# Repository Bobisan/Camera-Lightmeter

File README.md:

# Camera Light Meter
Светломер за фотоапарати, който измерва количеството светлина на околната среда, определя правилната експозиция за снимките и пресмята стойностите на настройките, нужни за нея. Вмомента функцоионално работи, но е на breadboard, има неудобни контроли, работи само сързан към захранване и има неоптимизиран код, който води до проблеми. Целта ни е да намалим цялостният размер на проекта и да увеличим неговата надеждност, като го направим на печатна платка и му 3D принтираме корпус, да подобрим и сменим някои от използваните компоненти, като екрана, който смятаме да сменим с някой по-малък и с по-висока резолюция, и бутоните, които смятаме да сменим с ротационни енкодери за по-компактен и удобен дизайн, и смятаме да го направим да работи на презареждаема батерия.

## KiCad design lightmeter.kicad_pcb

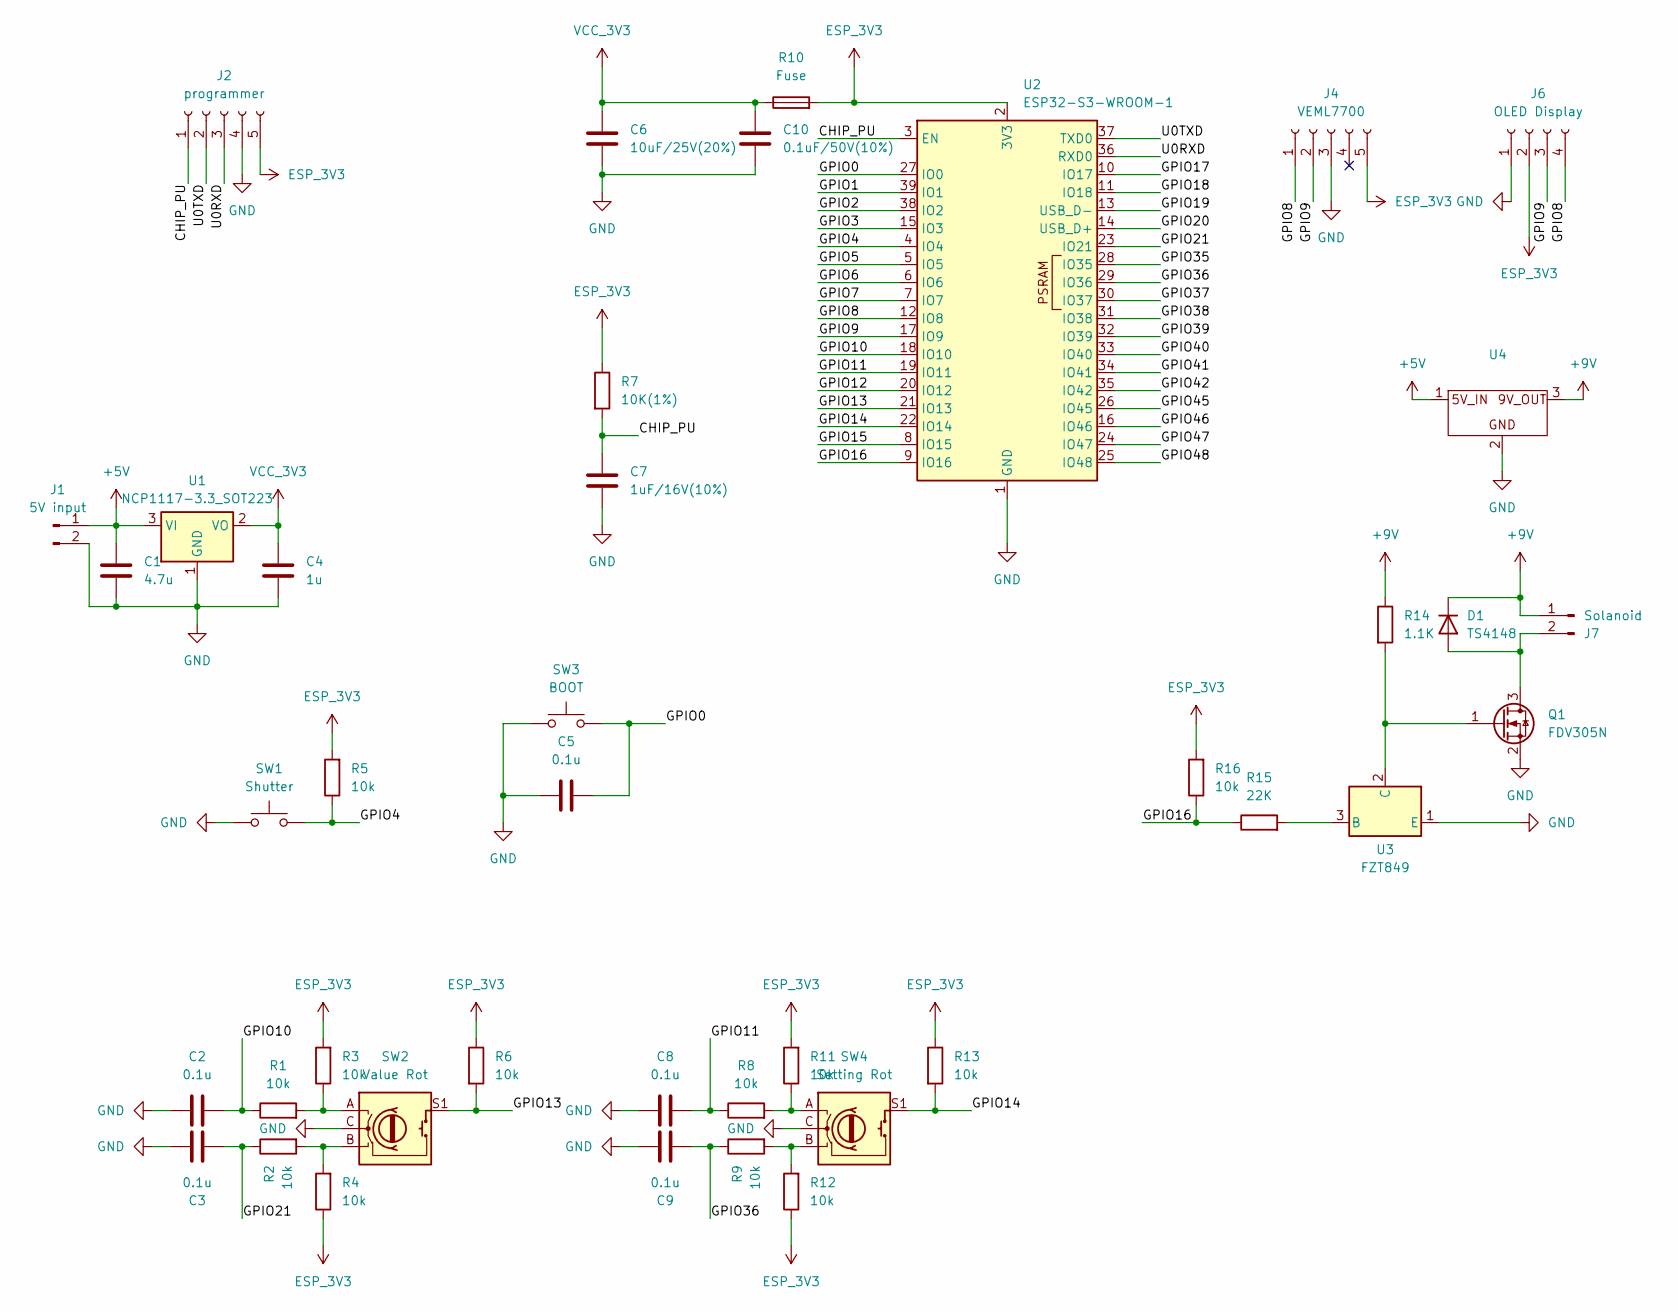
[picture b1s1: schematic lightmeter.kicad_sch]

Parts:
C1: 4.7u; C_0805_2012Metric
C2, C3, C5, C8, C9: 0.1u; C_0805_2012Metric
C4: 1u; C_0805_2012Metric
C6: 10uF/25V(20%); C_0805_2012Metric
C7: 1uF/16V(10%); C_0805_2012Metric
C10: 0.1uF/50V(10%); C_0805_2012Metric
D1: TS4148; D_0805_2012Metric
J1: 5V input; JST_EH_B2B-EH-A_1x02_P2.50mm_Vertical
J2: programmer; JST_EH_B5B-EH-A_1x05_P2.50mm_Vertical
J4: VEML7700; PinHeader_1x05_P2.54mm_Vertical
J6: OLED Display; JST_EH_B4B-EH-A_1x04_P2.50mm_Vertical
J7: Solanoid; JST_EH_B2B-EH-A_1x02_P2.50mm_Vertical
Q1: FDV305N; SOT-23
R1, R2, R3, R4, R5, R6, R8, R9, R11, R12, R13, R16: 10k; R_0805_2012Metric
R7: 10K(1%); R_0805_2012Metric
R10: Fuse; Fuse_1206_3216Metric
R14: 1.1K; R_0805_2012Metric
R15: 22K; R_0805_2012Metric
SW1: Shutter; Vertical_Push_Button
SW2: Value Rot; Rotary_JST
SW3: BOOT; SW_PUSH_1P1T_6x3.5mm_H4.3_APEM_MJTP1243
SW4: Setting Rot; Rotary_JST
U1: NCP1117-3.3_SOT223; SOT-223-3_TabPin2
U2: ESP32-S3-WROOM-1
U3: FZT849; SOT-223-3_TabPin2
U4: Boost_Converter_Module

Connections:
+5V: C1.1, J1.1, U1.3 (VI), U4.1
+9V: D1.1 (K), J7.1, R14.1, U4.3
/CHIP_PU: C7.1, J2.1, R7.2, U2.3 (EN)
/GPIO0: C5.2, SW3.2, U2.27 (IO0)
/GPIO1: U2.39 (IO1)
/GPIO2: U2.38 (IO2)
/GPIO3: U2.15 (IO3)
/GPIO4: R5.1, SW1.2, U2.4 (IO4)
/GPIO5: U2.5 (IO5)
/GPIO6: U2.6 (IO6)
/GPIO7: U2.7 (IO7)
/GPIO8: J4.1, J6.4, U2.12 (IO8)
/GPIO9: J4.2, J6.3, U2.17 (IO9)
/GPIO10: C2.2, R1.1, U2.18 (IO10)
/GPIO11: C8.2, R8.1, U2.19 (IO11)
/GPIO12: U2.20 (IO12)
/GPIO13: R6.2, SW2.S1, U2.21 (IO13)
/GPIO14: R13.2, SW4.S1, U2.22 (IO14)
/GPIO15: U2.8 (IO15)
/GPIO16: R15.1, R16.1, U2.9 (IO16)
/GPIO17: U2.10 (IO17)
/GPIO18: U2.11 (IO18)
/GPIO19: U2.13 (USB_D-)
/GPIO20: U2.14 (USB_D+)
/GPIO21: C3.2, R2.1, U2.23 (IO21)
/GPIO35: U2.28 (IO35)
/GPIO36: C9.2, R9.1, U2.29 (IO36)
/GPIO37: U2.30 (IO37)
/GPIO38: U2.31 (IO38)
/GPIO39: U2.32 (IO39)
/GPIO40: U2.33 (IO40)
/GPIO41: U2.34 (IO41)
/GPIO42: U2.35 (IO42)
/GPIO45: U2.26 (IO45)
/GPIO46: U2.16 (IO46)
/GPIO47: U2.24 (IO47)
/GPIO48: U2.25 (IO48)
/U0RXD: J2.3, U2.36 (RXD0)
/U0TXD: J2.2, U2.37 (TXD0)
ESP_3V3: J2.5, J4.5, J6.2, R3.2, R4.1, R5.2, R6.1, R7.1, R10.2, R11.2, R12.1, R13.1, R16.2, U2.2 (3V3)
GND: C1.2, C2.1, C3.1, C4.2, C5.1, C6.2, C7.2, C8.1, C9.1, C10.2, J1.2, J2.4, J4.3, J6.1, Q1.2 (S), SW1.1, SW2.C, SW3.1, SW4.C, U1.1 (GND), U2.1 (GND), U2.40 (GND), U2.41 (GND), U3.1 (E), U4.2
unnamed: D1.2 (A), J7.2, Q1.3 (D)
unnamed: Q1.1 (G), R14.2, U3.2 (C)
unnamed: R1.2, R3.1, SW2.A
unnamed: R2.2, R4.2, SW2.B
unnamed: R8.2, R11.1, SW4.A
unnamed: R9.2, R12.2, SW4.B
unnamed: R15.2, U3.3 (B)
VCC_3V3: C4.1, C6.1, C10.1, R10.1, U1.2 (VO)

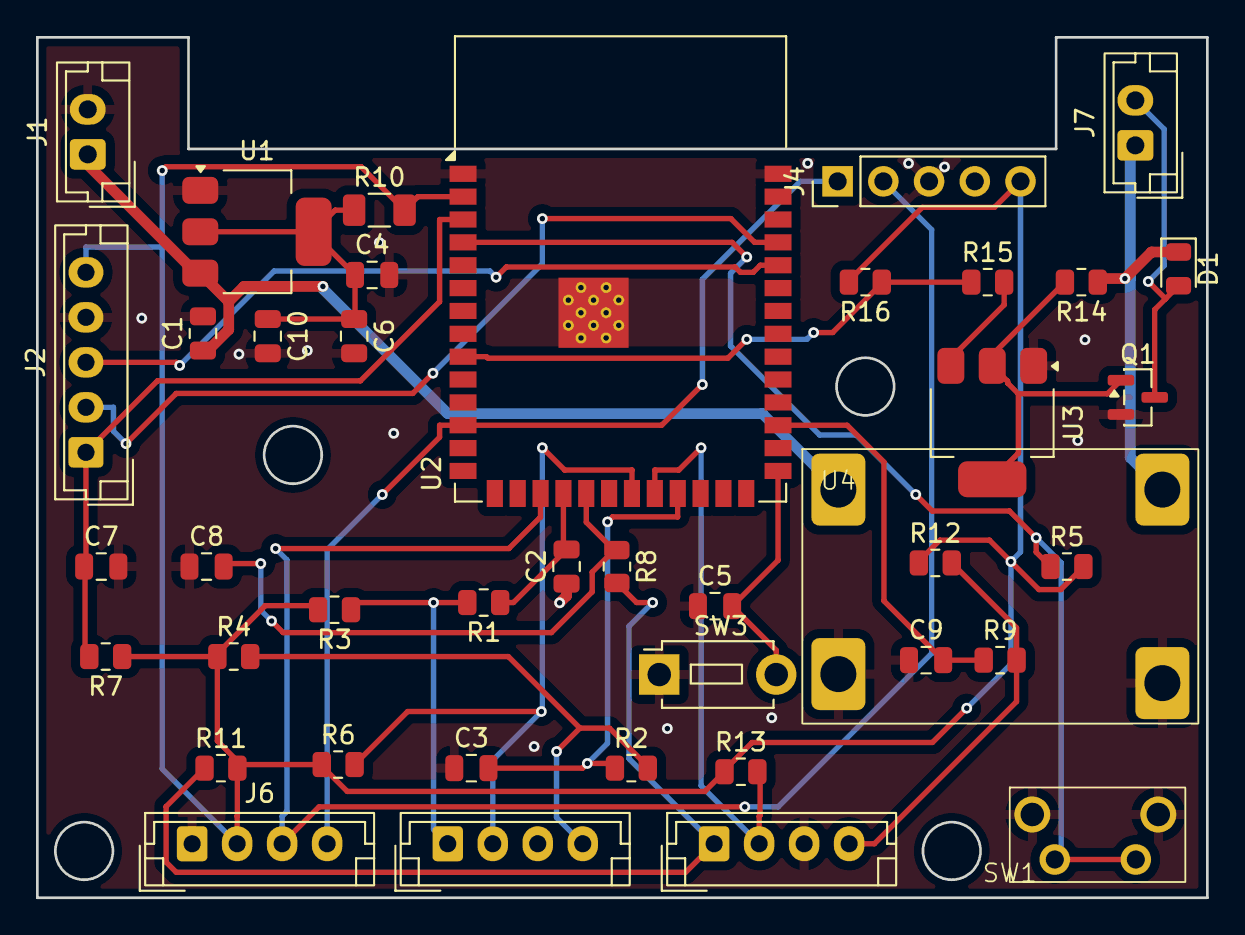
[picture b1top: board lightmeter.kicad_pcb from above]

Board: 2 copper layers, 65.0 x 47.8 mm, 41 parts (0 on the bottom side), 26 nets.

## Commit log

2025-04-25 Update Light_meter_arduino_code.ino
    working code for the project finally
2025-10-04 Changed for the new school year project
2025-10-19 Updated the dimension information for the project in the Goals.docx file
2025-10-19 Added the plan document
2025-10-26 Deleted Plan.docx to replace it
2025-10-26 Updating the goals and requirements
2026-02-15 Commiting all schematic and pcb files
2026-03-02 Add files via upload
    code progress. Need to read about shrift changes in size and all that other than that prototype rotter encoders should work
2026-03-02 Rename Light_meter_arduino_code.ino to Light_meter_arduino_nano_code.ino
2026-03-09 Commiting new branch
2026-03-09 Added power supply block to the schematic
2026-03-22 Added the Rotary encoders and the push buttons, that are going to be used, in the schematic.
2026-03-23 Finished schematic. Layout is next
2026-03-24 Replaced the usb C port with a connector for a programmer module
2026-03-24 Annotated the schematic
2026-03-31 Assigned footprints to all components
2026-04-03 Fixed the solanoid control part of the schematic as well as the connector for the VEML7700 light sensor, now I am really ready to start the layout proccess
2026-04-03 Fixed a few wrong footprints
2026-04-04 ixed even more issues with the footprints, configured placement and ran autorouter. Still have settings to adjust though.
2026-04-05 Finished PCB. I will review it one more time and send it for fabrication.
2026-04-08 Refactor light meter code and add VEML7700 support
2026-04-09 Finished board and exported production files
